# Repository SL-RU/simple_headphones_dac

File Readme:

Simple board with DAC cs4335 and amplifier TDA2822

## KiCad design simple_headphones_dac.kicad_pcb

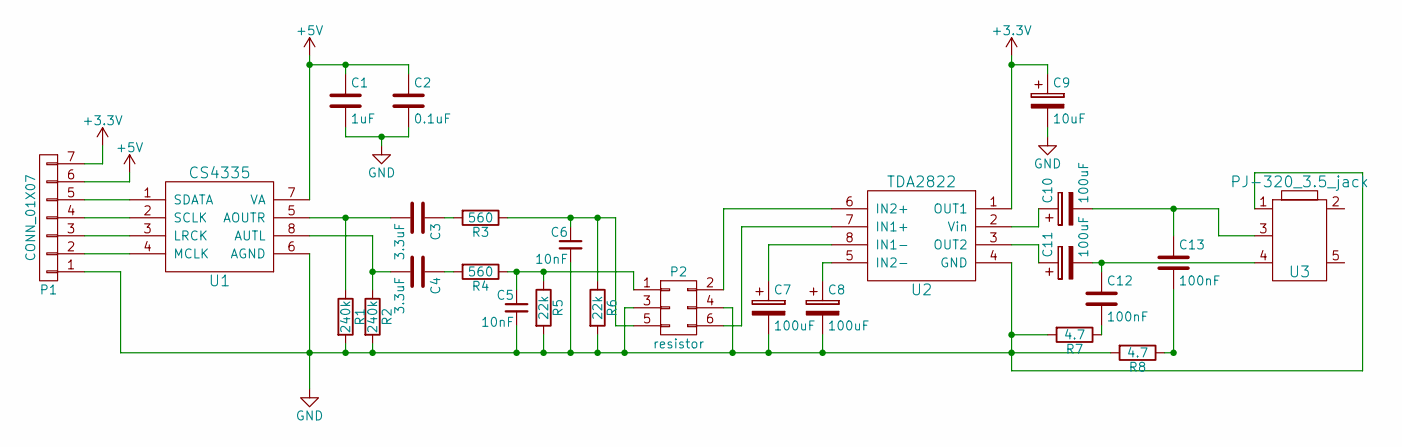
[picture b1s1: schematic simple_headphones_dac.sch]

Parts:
C1: 1uF; C_0805_HandSoldering
C2: 0.1uF; C_0402
C3, C4: 3.3uF; C_0805_HandSoldering
C5, C6: 10nF; C_0805_HandSoldering
C7, C8, C10, C11: 100uF; C_Radial_D6.3_L11.2_P2.5
C9: 10uF; C_Radial_D5_L11_P2
C12, C13: 100nF; C_0402
P1: CONN_01X07; Pin_Header_Straight_1x07
P2: resistor; Pin_Header_Straight_2x03
R1, R2: 240k; R_0603_HandSoldering
R3, R4: 560; R_0603_HandSoldering
R5, R6: 22k; R_0603_HandSoldering
R7, R8: 4.7; R_0603_HandSoldering
U1: CS4335; SOIC-8_3.9x4.9mm_Pitch1.27mm
U2: TDA2822; SO-8
U3: PJ-320_3.5_jack; PJ-320E

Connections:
+3V3: C9.1, P1.7, U2.1 (OUT1)
+5V: C1.1, C2.1, P1.6, U1.7 (VA)
GND: C1.2, C2.2, C5.2, C6.2, C7.2, C8.2, C9.2, P1.1, P2.3, P2.4, R1.2, R2.2, R5.2, R6.2, R7.2, R8.2, U1.6 (AGND), U2.4 (GND), U3.1
unnamed: C3.1, R3.2
unnamed: C3.2, R1.1, U1.5 (AOUTR)
unnamed: C4.1, R4.2
unnamed: C4.2, R2.1, U1.8 (AUTL)
unnamed: C5.1, P2.1, R4.1, R5.1
unnamed: C6.1, P2.5, R3.1, R6.1
unnamed: C7.1, U2.8 (IN1-)
unnamed: C8.1, U2.5 (IN2-)
unnamed: C10.1, U2.2 (Vin)
unnamed: C10.2, C13.1, U3.3
unnamed: C11.1, U2.3 (OUT2)
unnamed: C11.2, C12.1, U3.4
unnamed: C12.2, R7.1
unnamed: C13.2, R8.1
unnamed: P1.2, U1.4 (MCLK)
unnamed: P1.3, U1.3 (LRCK)
unnamed: P1.4, U1.2 (SCLK)
unnamed: P1.5, U1.1 (SDATA)
unnamed: P2.2, U2.6 (IN2+)
unnamed: P2.6, U2.7 (IN1+)

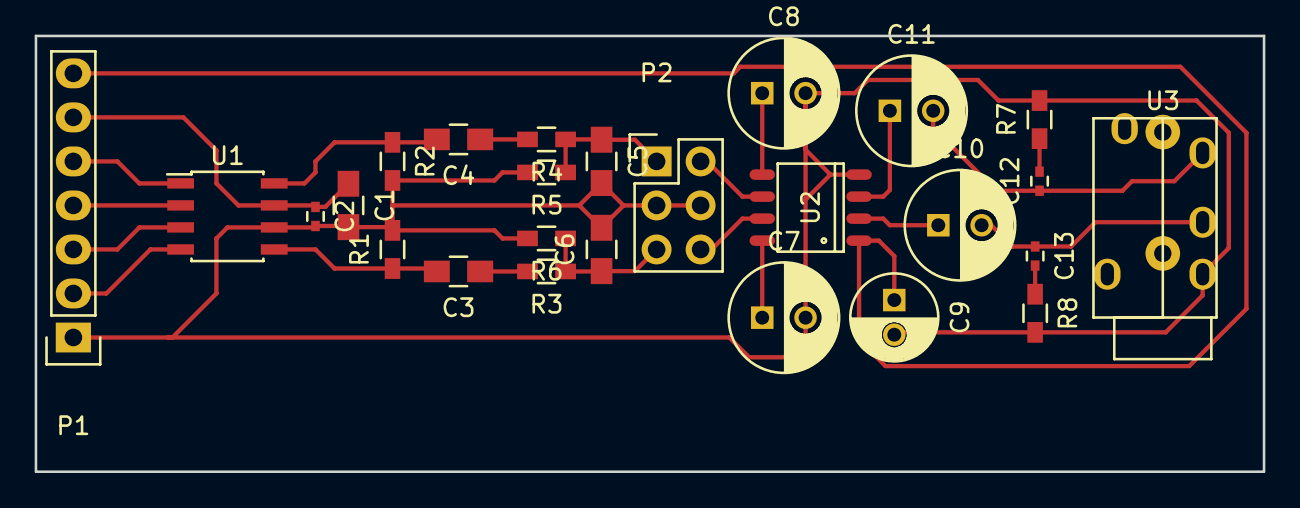
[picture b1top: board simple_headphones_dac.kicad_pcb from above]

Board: 2 copper layers, 70.9 x 25.1 mm, 26 parts (0 on the bottom side), 23 nets.

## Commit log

2016-08-02 first
2016-08-16 dac+amplifier
